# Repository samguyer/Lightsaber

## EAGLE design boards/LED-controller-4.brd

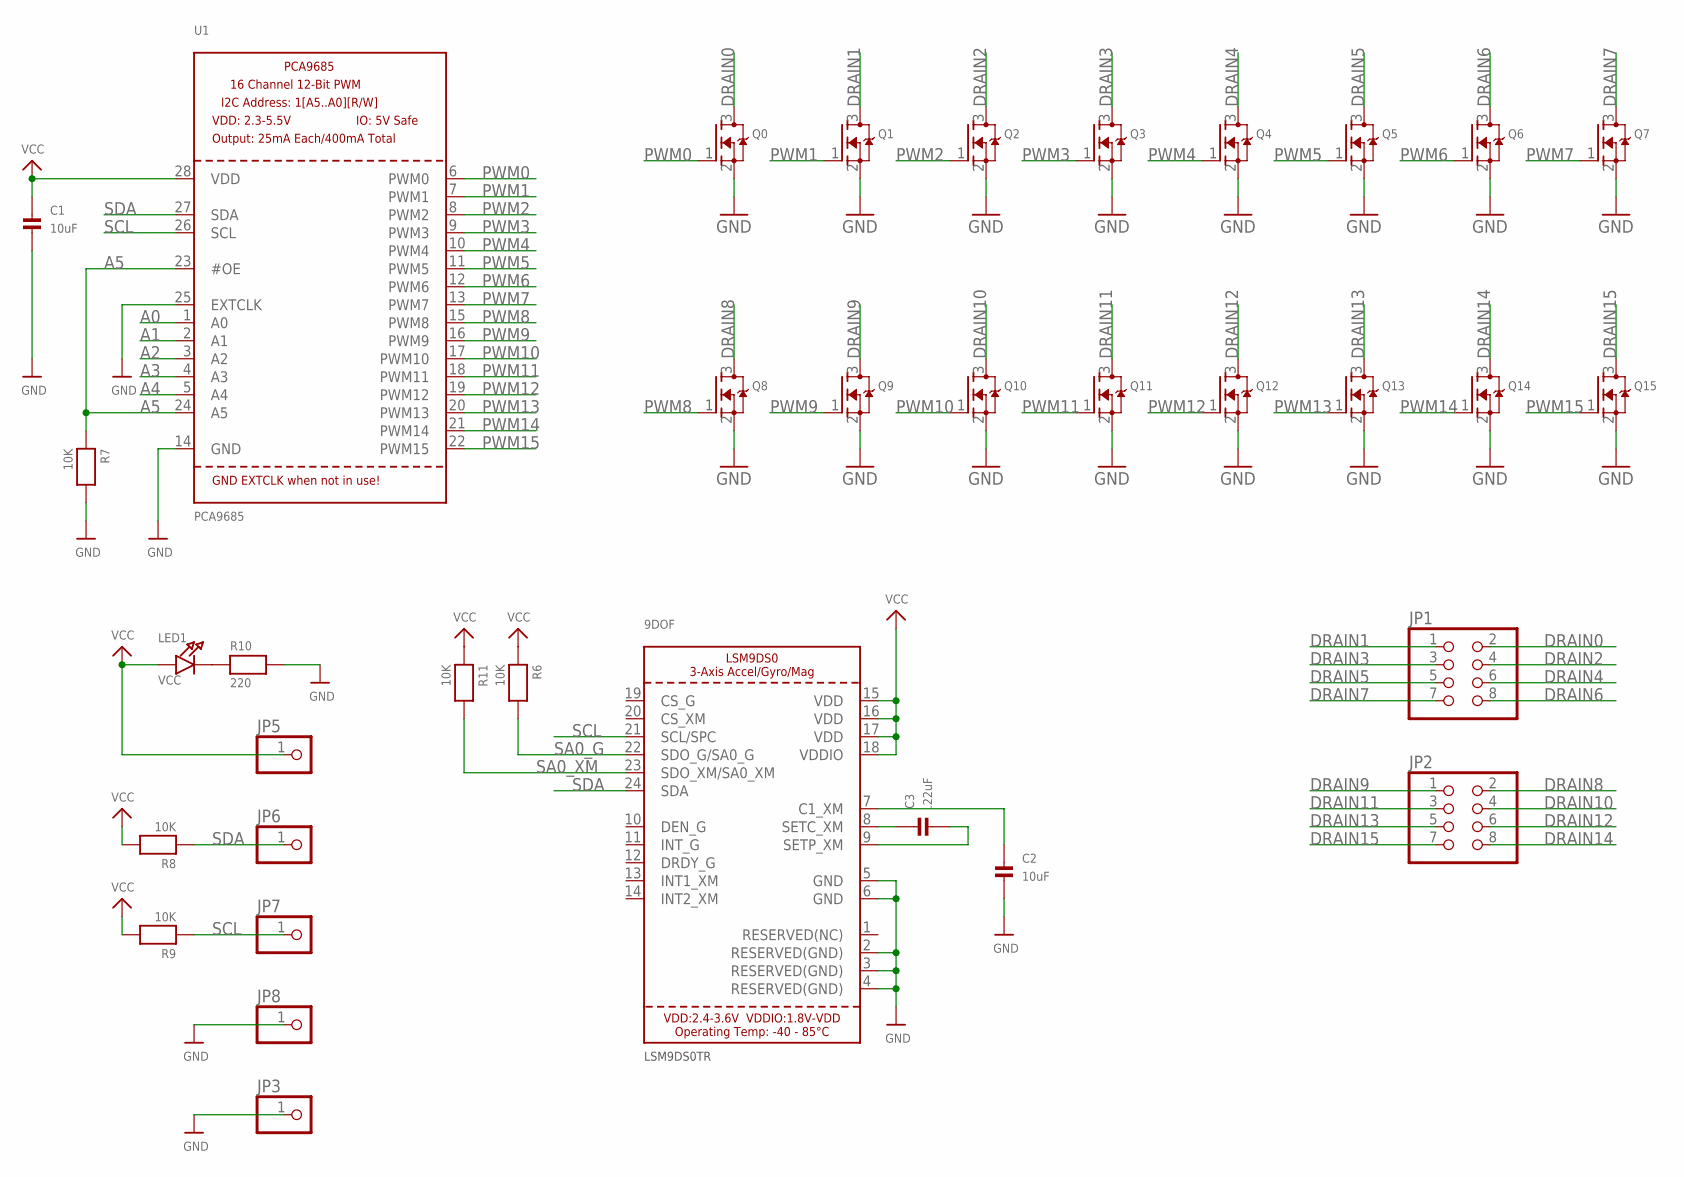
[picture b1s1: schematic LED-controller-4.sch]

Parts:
9DOF: LSM9DS0TR; LGA24_4X4MM
C1, C2: 10uF; 0805
C3: .22uF; 0805
JP1, JP2: PINHD-2X4; 2X04
JP3, JP5, JP6, JP7, JP8: PINHD-1X1CB; 1X01-CLEANBIG
LED1: VCC; CHIPLED_0805
Q0, Q1, Q2, Q3, Q4, Q5, Q6, Q7, Q8, Q9, Q10, Q11, Q12, Q13, Q14, Q15: MOSFET-NREFLOW; SOT23
R6, R7, R8, R9, R11: 10K; 0603
R10: 220; 0603
U1: PCA9685; TSSOP28

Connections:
A0: U1.1 (A0)
A1: U1.2 (A1)
A2: U1.3 (A2)
A3: U1.4 (A3)
A4: U1.5 (A4)
A5: R7.1, U1.23 (#OE), U1.24 (A5)
DRAIN0: JP1.2, Q0.3 (D)
DRAIN1: JP1.1, Q1.3 (D)
DRAIN2: JP1.4, Q2.3 (D)
DRAIN3: JP1.3, Q3.3 (D)
DRAIN4: JP1.6, Q4.3 (D)
DRAIN5: JP1.5, Q5.3 (D)
DRAIN6: JP1.8, Q6.3 (D)
DRAIN7: JP1.7, Q7.3 (D)
DRAIN8: JP2.2, Q8.3 (D)
DRAIN9: JP2.1, Q9.3 (D)
DRAIN10: JP2.4, Q10.3 (D)
DRAIN11: JP2.3, Q11.3 (D)
DRAIN12: JP2.6, Q12.3 (D)
DRAIN13: JP2.5, Q13.3 (D)
DRAIN14: JP2.8, Q14.3 (D)
DRAIN15: JP2.7, Q15.3 (D)
GND: 9DOF.2 (RESERVED(GND)), 9DOF.3 (RESERVED(GND)), 9DOF.4 (RESERVED(GND)), 9DOF.5 (GND), 9DOF.6 (GND), C1.2, C2.2, JP3.1, JP8.1, Q0.2 (S), Q1.2 (S), Q2.2 (S), Q3.2 (S), Q4.2 (S), Q5.2 (S), Q6.2 (S), Q7.2 (S), Q8.2 (S), Q9.2 (S), Q10.2 (S), Q11.2 (S), Q12.2 (S), Q13.2 (S), Q14.2 (S), Q15.2 (S), R7.2, R10.2, U1.14 (GND), U1.25 (EXTCLK)
unnamed: LED1.C, R10.1
unnamed: 9DOF.8 (SETC_XM), C3.1
unnamed: 9DOF.9 (SETP_XM), C3.2
unnamed: 9DOF.7 (C1_XM), C2.1
PWM0: Q0.1 (G), U1.6 (PWM0)
PWM1: Q1.1 (G), U1.7 (PWM1)
PWM2: Q2.1 (G), U1.8 (PWM2)
PWM3: Q3.1 (G), U1.9 (PWM3)
PWM4: Q4.1 (G), U1.10 (PWM4)
PWM5: Q5.1 (G), U1.11 (PWM5)
PWM6: Q6.1 (G), U1.12 (PWM6)
PWM7: Q7.1 (G), U1.13 (PWM7)
PWM8: Q8.1 (G), U1.15 (PWM8)
PWM9: Q9.1 (G), U1.16 (PWM9)
PWM10: Q10.1 (G), U1.17 (PWM10)
PWM11: Q11.1 (G), U1.18 (PWM11)
PWM12: Q12.1 (G), U1.19 (PWM12)
PWM13: Q13.1 (G), U1.20 (PWM13)
PWM14: Q14.1 (G), U1.21 (PWM14)
PWM15: Q15.1 (G), U1.22 (PWM15)
SA0_G: 9DOF.22 (SDO_G/SA0_G), R6.2
SA0_XM: 9DOF.23 (SDO_XM/SA0_XM), R11.2
SCL: 9DOF.21 (SCL/SPC), JP7.1, R9.1, U1.26 (SCL)
SDA: 9DOF.24 (SDA), JP6.1, R8.1, U1.27 (SDA)
VCC: 9DOF.15 (VDD), 9DOF.16 (VDD), 9DOF.17 (VDD), 9DOF.18 (VDDIO), C1.1, JP5.1, LED1.A, R6.1, R8.2, R9.2, R11.1, U1.28 (VDD)

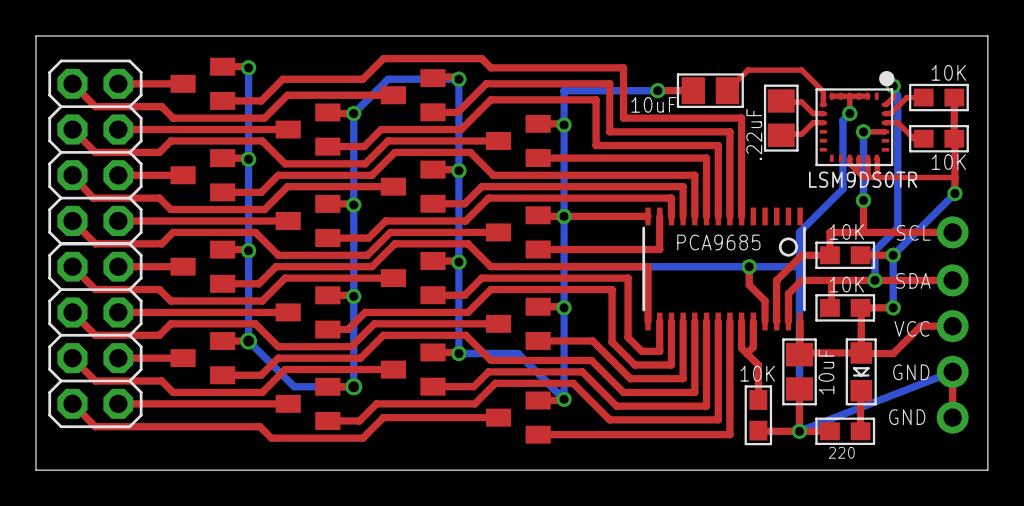
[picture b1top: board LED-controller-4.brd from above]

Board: 2 copper layers, 52.9 x 24.1 mm, 35 parts (0 on the bottom side), 43 nets.

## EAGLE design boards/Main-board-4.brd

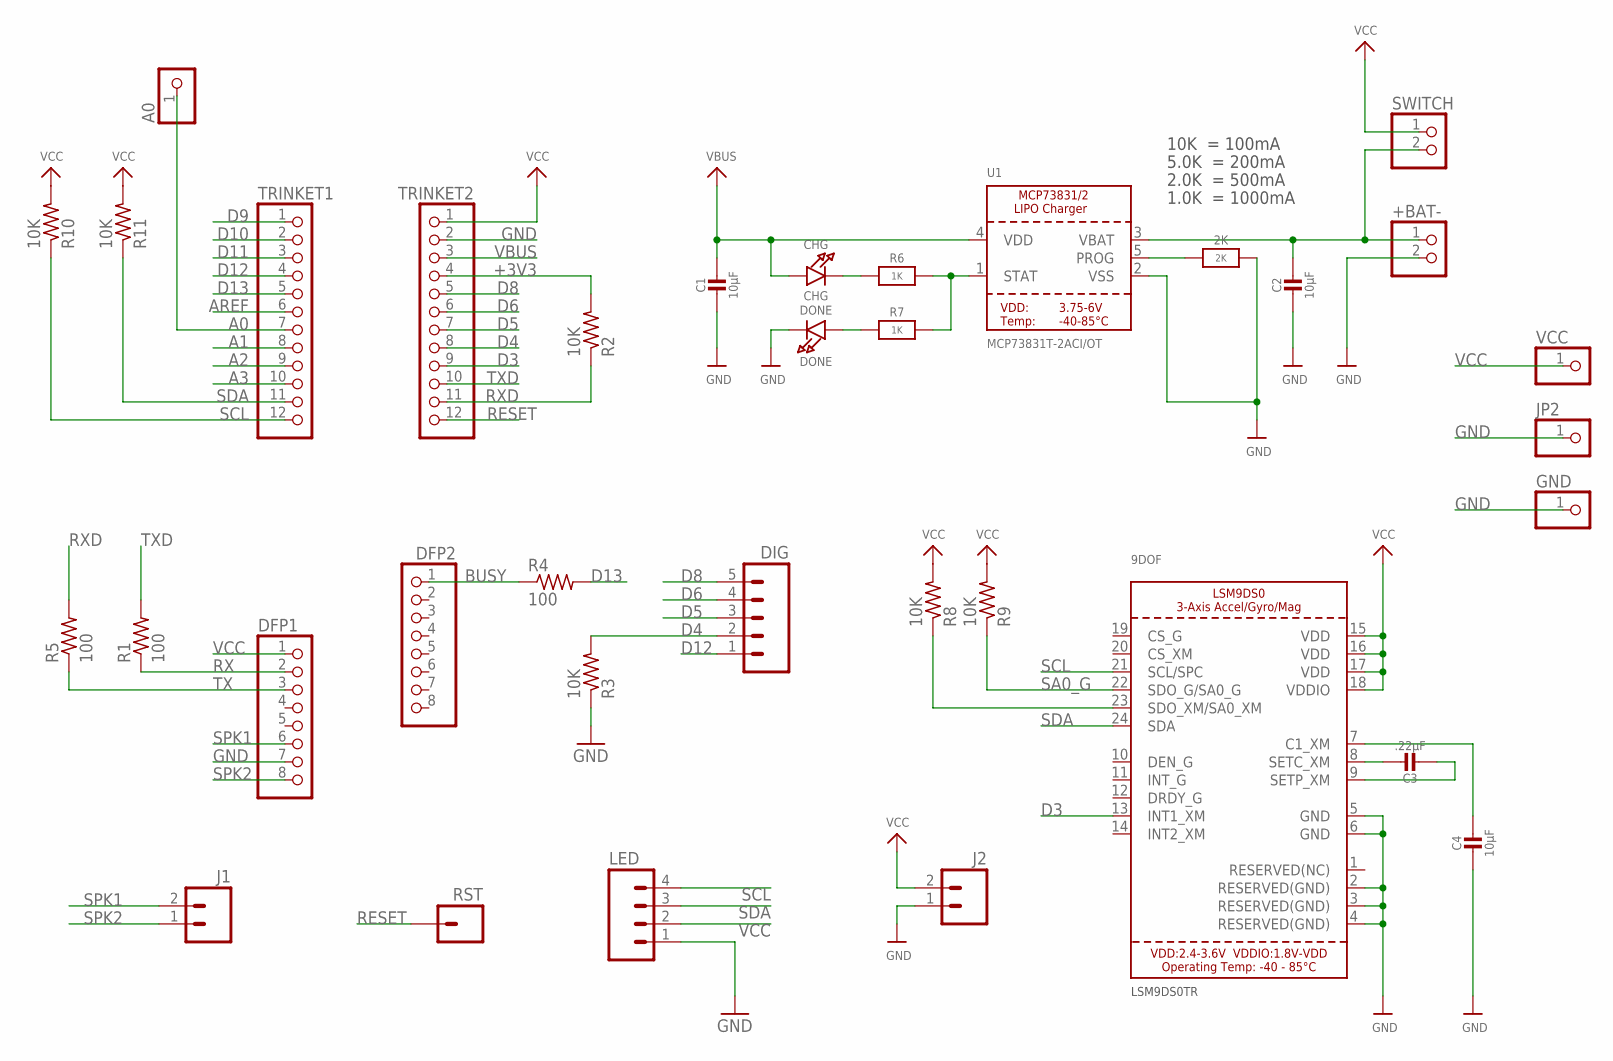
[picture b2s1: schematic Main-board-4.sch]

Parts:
2K: 2K; _0805MP
9DOF: LSM9DS0TR; LGA24_4X4MM
+BAT-: HEADER-1X2ROUND; 1X02_ROUND
A0: PINHD-1X1CB; 1X01-CLEANBIG
C1, C2, C4: 10µF; 0805-NO
C3: .22µF; 0805-NO
CHG: CHG; CHIPLED_0805_NOOUTLINE
DFP1, DFP2: PINHD-1X8CLEANBIG; 1X08-CLEANBIG
DIG: M05NO_SILK; 1X05_NO_SILK
DONE: DONE; CHIPLED_0805_NOOUTLINE
GND: PINHD-1X1CB; 1X01-CLEANBIG
J1, J2: M021X02_NO_SILK; 1X02_NO_SILK
JP2: PINHD-1X1CB; 1X01-CLEANBIG
LED: M04NO_SILK_ALL_ROUND; 1X04_NO_SILK_ALL_ROUND
R1, R4, R5: 100; R0805
R2, R3, R8, R9, R10, R11: 10K; R0805
R6, R7: 1K; 0805-NO
RST: M01PTH_NO_SILK_YES_STOP; 1X01_NO_SILK
SWITCH: HEADER-1X2ROUND; 1X02_ROUND
TRINKET1, TRINKET2: PINHD-1X12-CB; 1X12-CB
U1: MCP73831T-2ACI/OT; SOT23-5
VCC: PINHD-1X1CB; 1X01-CLEANBIG

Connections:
+3V3: R2.2, TRINKET2.4
A0: A0.1, TRINKET1.7
A1: TRINKET1.8
A2: TRINKET1.9
A3: TRINKET1.10
AREF: TRINKET1.6
BUSY: DFP2.1, R4.1
D3: 9DOF.13 (INT1_XM), TRINKET2.9
D4: DIG.2, R3.2, TRINKET2.8
D5: DIG.3, TRINKET2.7
D6: DIG.4, TRINKET2.6
D8: DIG.5, TRINKET2.5
D9: TRINKET1.1
D10: TRINKET1.2
D11: TRINKET1.3
D12: DIG.1, TRINKET1.4
D13: R4.2, TRINKET1.5
GND: 2K.2, 9DOF.2 (RESERVED(GND)), 9DOF.3 (RESERVED(GND)), 9DOF.4 (RESERVED(GND)), 9DOF.5 (GND), 9DOF.6 (GND), +BAT-.2, C1.2, C2.2, C4.2, DFP1.7, DONE.C, GND.1, J2.1, JP2.1, LED.1, R3.1, TRINKET2.2, U1.2 (VSS)
unnamed: CHG.C, R6.1
unnamed: R6.2, R7.2, U1.1 (STAT)
unnamed: 9DOF.8 (SETC_XM), C3.1
unnamed: +BAT-.1, C2.1, SWITCH.2, U1.3 (VBAT)
unnamed: 2K.1, U1.5 (PROG)
unnamed: DONE.A, R7.1
unnamed: 9DOF.9 (SETP_XM), C3.2
unnamed: 9DOF.7 (C1_XM), C4.1
RESET: RST.1, TRINKET2.12
RX: DFP1.2, R1.1
RXD: R2.1, R5.2, TRINKET2.11
SA0_G: 9DOF.22 (SDO_G/SA0_G), R9.1
SA0_XM: 9DOF.23 (SDO_XM/SA0_XM), R8.1
SCL: 9DOF.21 (SCL/SPC), LED.4, R10.1, TRINKET1.12
SDA: 9DOF.24 (SDA), LED.3, R11.1, TRINKET1.11
SPK1: DFP1.6, J1.2
SPK2: DFP1.8, J1.1
TX: DFP1.3, R5.1
TXD: R1.2, TRINKET2.10
VBUS: C1.1, CHG.A, TRINKET2.3, U1.4 (VDD)
VCC: 9DOF.15 (VDD), 9DOF.16 (VDD), 9DOF.17 (VDD), 9DOF.18 (VDDIO), DFP1.1, J2.2, LED.2, R8.2, R9.2, R10.2, R11.2, SWITCH.1, TRINKET2.1, VCC.1

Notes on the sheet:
10K = 100mA
5.0K = 200mA
2.0K = 500mA
1.0K = 1000mA

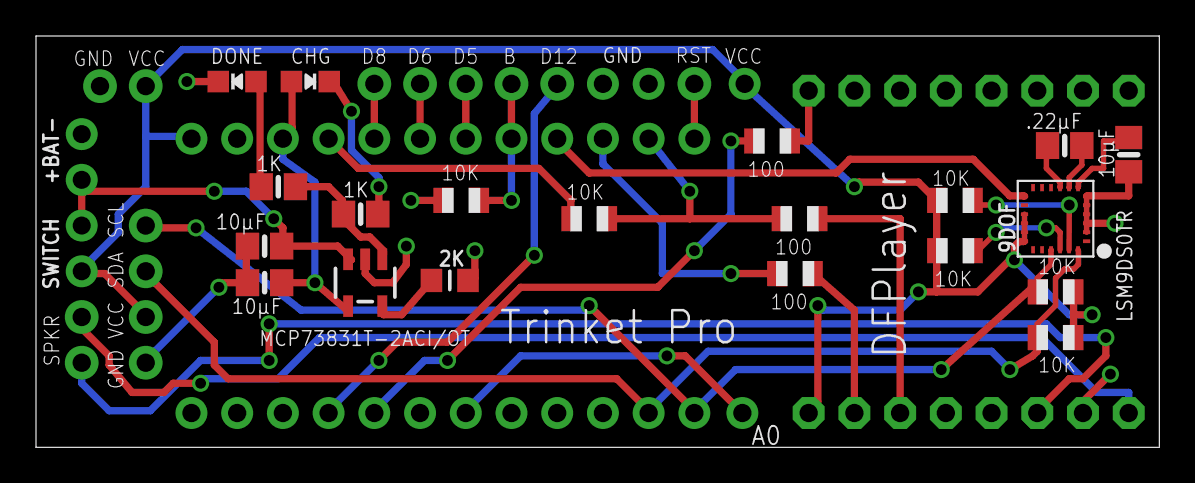
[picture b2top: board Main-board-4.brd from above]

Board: 2 copper layers, 62.4 x 22.9 mm, 35 parts (0 on the bottom side), 32 nets.

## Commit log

2016-10-03 Starting lightsaber repo
2016-11-09 Added hilt template
2017-03-24 Recent updates
    Added the boards

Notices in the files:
parts and their libraries:
SparkFun-Connectors: Licensing: Creative Commons ShareAlike 4.0 International - https://creativecommons.org/licenses/by-sa/4.0
microbuilder: This work is placed in the public domain, and may be freely used for commercial and non-commercial work with the following conditions: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
